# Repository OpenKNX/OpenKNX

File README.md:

# OpenKNX
OpenSource KNX software and hardware for maker, hobbyist and home automation enthusiasts

[Find all information in the Wiki](https://github.com/OpenKNX/OpenKNX/wiki)

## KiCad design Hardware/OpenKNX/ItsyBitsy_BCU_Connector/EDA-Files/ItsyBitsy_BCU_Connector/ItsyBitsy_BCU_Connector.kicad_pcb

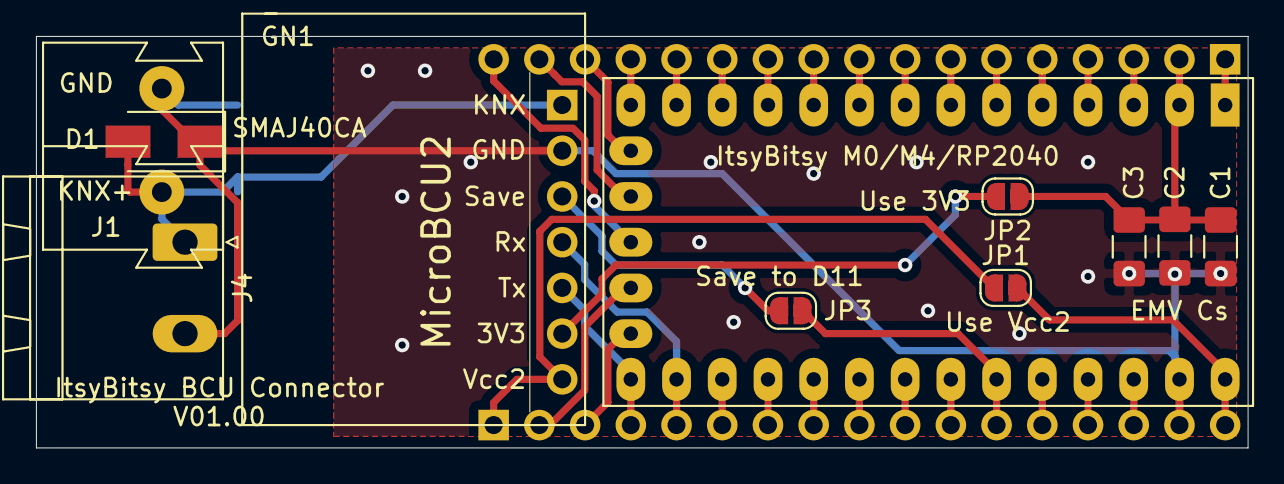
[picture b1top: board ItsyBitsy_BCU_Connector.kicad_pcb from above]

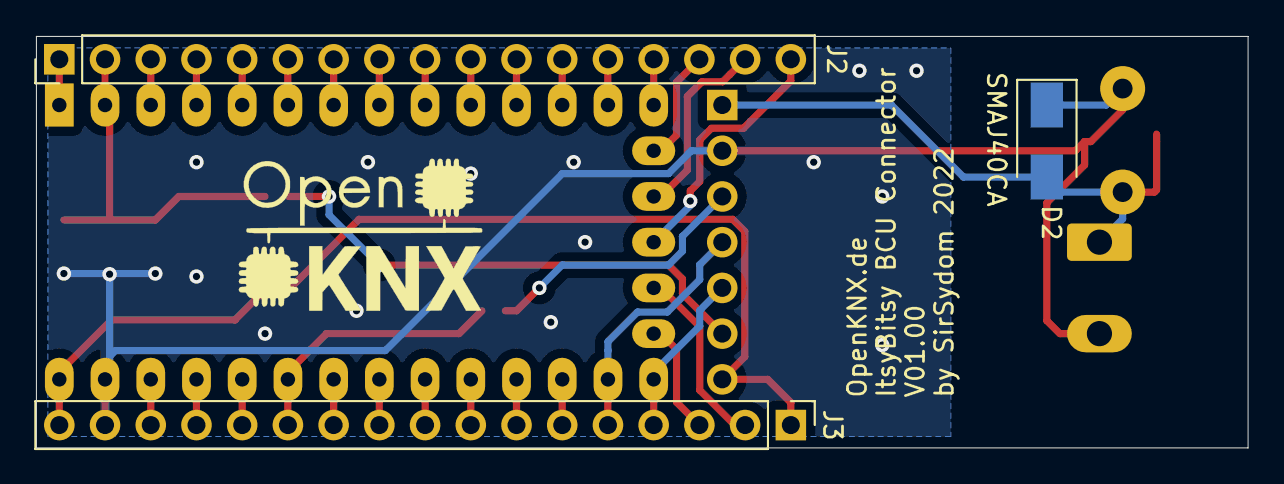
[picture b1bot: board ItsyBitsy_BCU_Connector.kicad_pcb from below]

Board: 2 copper layers, 67.3 x 22.9 mm, 14 parts (3 on the bottom side), 37 nets.

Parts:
C1, C2, C3: C; C_1206_3216Metric_Pad1.42x1.75mm_HandSolder
D1, D2: D_TVS; D_SMA
GN1: Konnekting_µBCU; MicroBCU2_PinSocket
GN2: ItsyBitsyM0
J1: Conn_KNX; KNX_Connector
J2, J3: Conn_01x17_Male; PinHeader_1x17_P2.54mm_Vertical
J4: Conn_KNX; PhoenixContact_MSTBA_2,5_2-G-5,08_1x02_P5.08mm_Horizontal
JP1, JP2, JP3: SolderJumper_2_Open; SolderJumper-2_P1.3mm_Open_RoundedPad1.0x1.5mm

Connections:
GND: C1.2, C2.2, C3.2, D1.1, D2.1, GN1.2, GN2.27, J1.2, J3.16, J4.2
unnamed: C1.1, C2.1, C3.1, GN2.2, J2.2, JP2.2
unnamed: D1.2, D2.2, GN1.1, J1.1, J4.1
unnamed: GN1.3, JP3.1
unnamed: GN1.6, JP2.1
unnamed: GN2.1, J2.1
unnamed: GN2.3, J2.3
unnamed: GN2.4, J2.4
unnamed: GN2.5, J2.5
unnamed: GN2.6, J2.6
unnamed: GN2.7, J2.7
unnamed: GN2.8, J2.8
unnamed: GN2.9, J2.9
unnamed: GN2.10, J2.10
unnamed: GN2.11, J2.11
unnamed: GN2.12, J2.12
unnamed: GN2.13, J2.13
unnamed: GN2.14, J2.14
unnamed: GN2.17, J3.6
unnamed: GN2.18, J3.7
unnamed: GN2.19, J3.8
unnamed: GN2.20, J3.9
unnamed: GN2.21, J3.10
unnamed: GN2.22, J3.11
unnamed: GN2.23, J3.12, JP3.2
unnamed: GN2.24, J3.13
unnamed: GN2.25, J3.14
unnamed: GN2.26, J3.15
unnamed: GN2.28, J3.17, JP1.2
unnamed: GN2.29, J2.15
unnamed: GN2.30, J2.16
unnamed: GN2.31, J2.17
unnamed: GN2.32, J3.2
unnamed: GN2.33, J3.3
Rx: GN1.5, GN2.15, J3.4
Tx: GN1.4, GN2.16, J3.5
Vcc2: GN1.7, J3.1, JP1.1

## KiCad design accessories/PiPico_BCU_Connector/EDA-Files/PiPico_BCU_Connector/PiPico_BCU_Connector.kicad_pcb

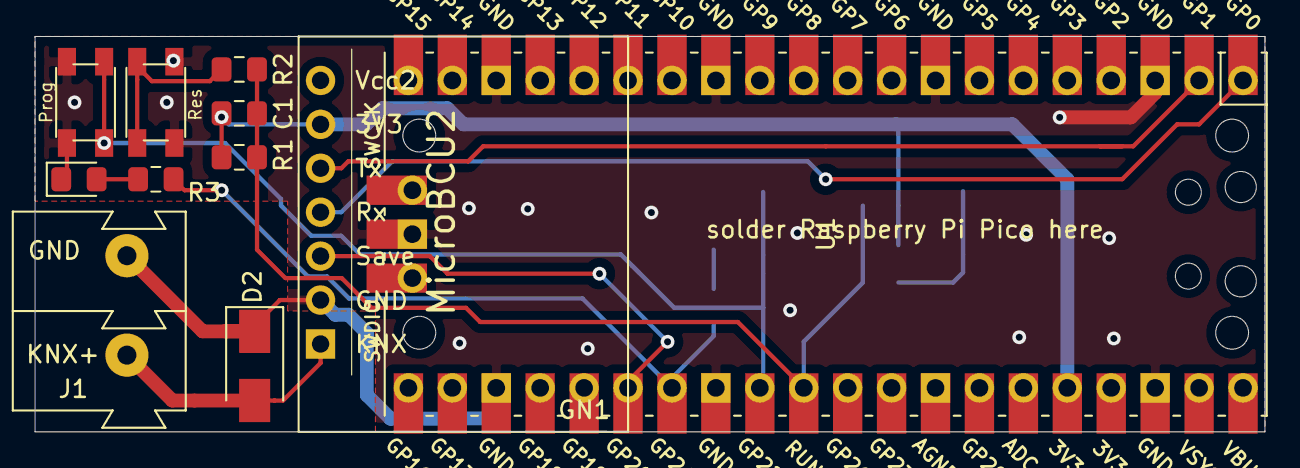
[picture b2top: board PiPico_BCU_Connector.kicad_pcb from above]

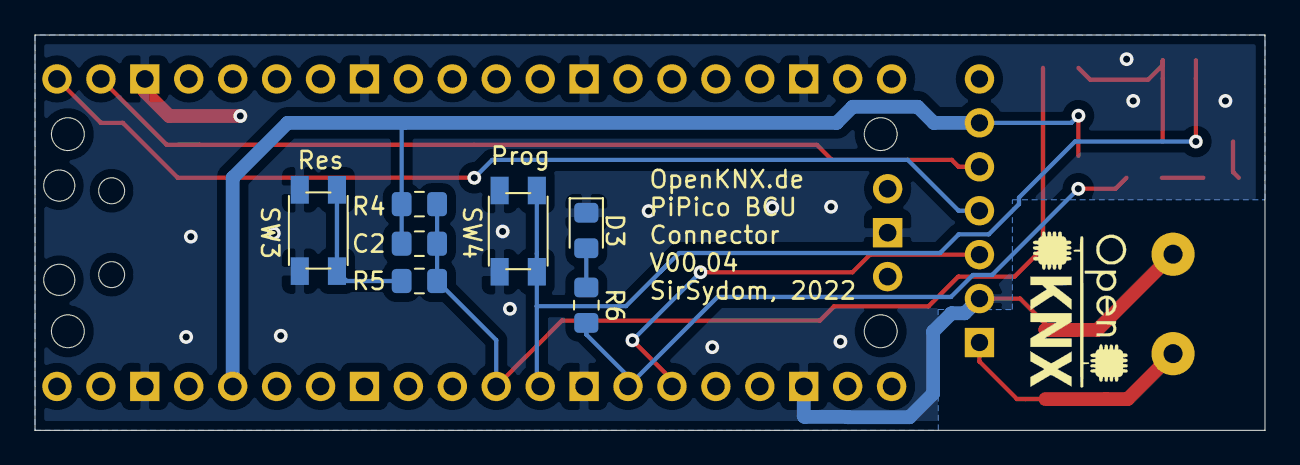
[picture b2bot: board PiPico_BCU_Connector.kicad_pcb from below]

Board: 2 copper layers, 71.1 x 22.9 mm, 18 parts (7 on the bottom side), 13 nets.

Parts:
C1, C2: 330pF; C_0805_2012Metric_Pad1.15x1.40mm_HandSolder
D1, D3: LED; D_0805_2012Metric_Pad1.15x1.40mm_HandSolder
D2: D_TVS; D_SMA
GN1: Konnekting_µBCU; MicroBCU2_PinSocket_LowProfile
J1: Conn_KNX; KNX_Connector
R1, R4: 2k2; R_0805_2012Metric_Pad1.15x1.40mm_HandSolder
R2, R5: 220; R_0805_2012Metric_Pad1.15x1.40mm_HandSolder
R3, R6: 1k; R_0805_2012Metric_Pad1.15x1.40mm_HandSolder
SW1, SW4: Prog; SW_Push_Xunpu_TS-1089S_Handsolder
SW2, SW3: Res; SW_Push_Xunpu_TS-1089S_Handsolder
U1: Pico; RPi_Pico_SMD_TH

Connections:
+3V3: C1.1, C2.1, GN1.6, R1.1, R4.1, U1.36
GND: D1.1, D2.1, D3.1, GN1.2, J1.2, SW1.2, SW2.2, SW3.2, SW4.2, U1.3, U1.8, U1.13, U1.18, U1.23, U1.28, U1.38, U1.42
unnamed: D1.2, R3.1
unnamed: D2.2, GN1.1, J1.1
unnamed: D3.2, R6.1
unnamed: GN1.3, U1.26
unnamed: R2.1, SW2.1
unnamed: R3.2, R6.2, U1.27
unnamed: R5.1, SW3.1
PROG: SW1.1, SW4.1, U1.29
RUN: C1.2, C2.2, R1.2, R2.2, R4.2, R5.2, U1.30
Rx: GN1.5, U1.2
Tx: GN1.4, U1.1

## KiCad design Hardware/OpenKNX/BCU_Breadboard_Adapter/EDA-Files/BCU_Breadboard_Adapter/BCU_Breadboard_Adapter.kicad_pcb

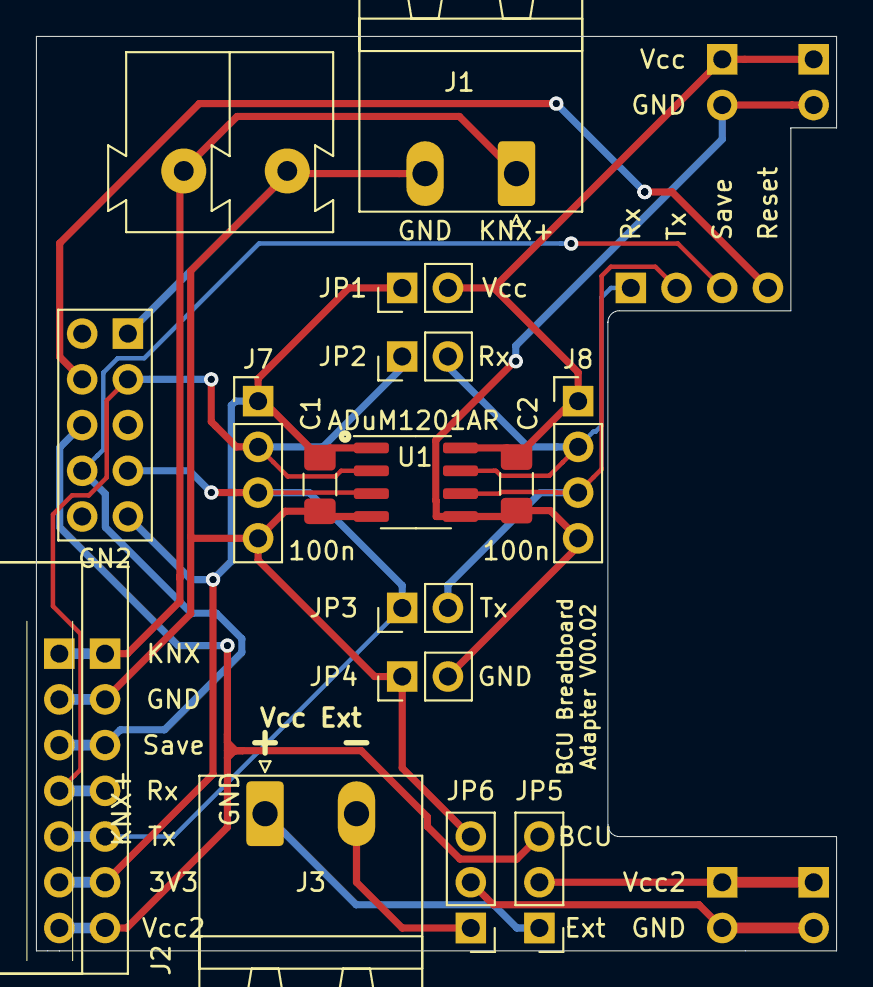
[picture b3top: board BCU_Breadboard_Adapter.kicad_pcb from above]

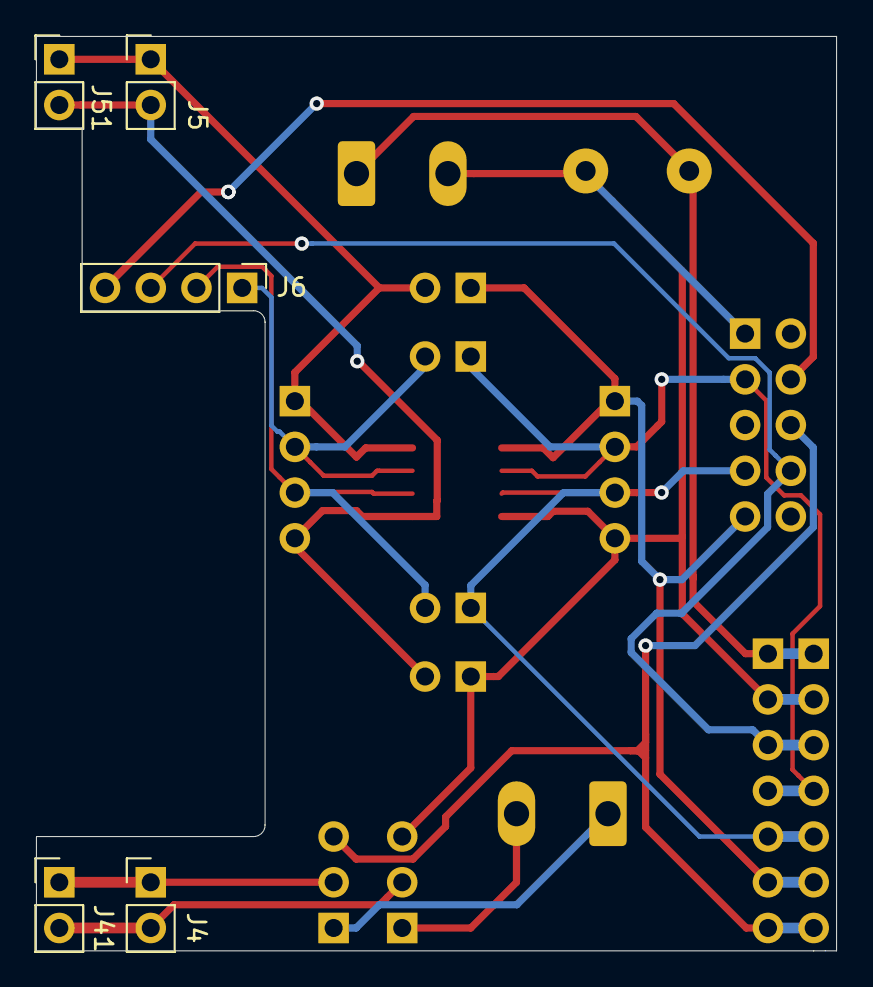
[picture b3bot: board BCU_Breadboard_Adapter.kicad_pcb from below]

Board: 2 copper layers, 44.5 x 50.8 mm, 22 parts (5 on the bottom side), 16 nets.

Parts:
C1, C2: 100n; C_1206_3216Metric_Pad1.42x1.75mm_HandSolder
GN1, GN3: Konnekting_µBCU; Konnekting_BCU
GN2: Siemens_BCU; Siemens_UP117_12_flat_header_only
J1: KNX_CC; PhoenixContact_MSTBA_2,5_2-G-5,08_1x02_P5.08mm_Horizontal
J2: KNX_Wago; KNX_Connector
J3: VCC_Ext; PhoenixContact_MSTBA_2,5_2-G-5,08_1x02_P5.08mm_Horizontal
J4, J41: VCC_Bot; PinHeader_1x02_P2.54mm_Vertical
J5, J51: VCC_Top; PinHeader_1x02_P2.54mm_Vertical
J6: BCU_Logik; PinHeader_1x04_P2.54mm_Vertical
J7, J8: Conn_01x04; PinHeader_1x04_P2.54mm_Vertical
JP1, JP2, JP3, JP4: Jumper; PinHeader_1x02_P2.54mm_Vertical
JP5, JP6: Jumper_NC_Dual; PinHeader_1x03_P2.54mm_Vertical
U1: ADuM1201AR; SOIC-8_3.9x4.9mm_P1.27mm

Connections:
unnamed: C1.1, GN1.6, GN2.5, GN3.6, J7.1, JP1.1, U1.1
unnamed: C1.2, GN1.2, GN2.1, GN3.2, J1.2, J2.2, J7.4, JP4.1, JP6.3, U1.4
unnamed: C2.1, J5.1, J8.1, J51.1, JP1.2, U1.8
unnamed: C2.2, J5.2, J8.4, J51.2, JP4.2, U1.5
unnamed: GN1.1, GN3.1, J1.1, J2.1
unnamed: GN1.3, GN2.7, GN3.3, J6.3
unnamed: GN1.4, GN2.2, GN3.4, J7.2, JP2.1, U1.2
unnamed: GN1.5, GN2.4, GN3.5, J7.3, JP3.1, U1.3
unnamed: GN1.7, GN2.8, GN3.7, JP5.3
unnamed: GN2.9, J6.4
unnamed: J3.1, JP5.1
unnamed: J3.2, JP6.1
unnamed: J4.1, J41.1, JP5.2
unnamed: J4.2, J41.2, JP6.2
unnamed: J6.1, J8.2, JP2.2, U1.7
unnamed: J6.2, J8.3, JP3.2, U1.6

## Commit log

2022-02-02 added profile readme
2022-02-02 Revert last try
2022-02-10 Update README.md
    finished device naming scheme
2022-02-15 added doc of adapter PCBs
2022-02-15 added NanoBCU and MicroBCU2 doc
2022-02-15 added PiPico BCU Connector pictures
2022-02-15 added thumbnail
2022-02-16 added pic
2022-02-17 ItsyBitsy_BCU_Connector_V01.00
2022-02-17 added docu
2022-02-18 added measurement for SAVE pin
2022-10-14 added Pico case 001
2022-10-14 added pics
2022-10-15 added schematic
2022-10-15 improved PiPico Case
2022-10-15 changed knx connector geometry
2022-10-15 moved to CATIA subdir
2023-11-08 NanoBCU V02.00 documentation
2024-07-27 KiCAD project files of - PiPico BCU Adapter - ItsyBitsy BCU Adapter - BCU Breadboard Adapter
2025-01-01 - Restructured directories same as in "OGM-HardwareConfig". - Added AB-SmartHouse Switch Actuator schematics. - Prepared directory for Smart-MF.
2025-01-01 Renamed now using device ID as folder name.
2025-03-27 add Smartmf Schematics
2025-03-29 Added schematics of AB-SmartHouse devices.
2025-04-26 Added schematics for AB-SmartHouse constant voltage dimmers.
2025-04-26 Added schematics for AB-SmartHouse push buttons.
2025-07-11 Added AB-TCH-RND schematics.
2025-12-14 Updated LED dimmer schematics.
2026-02-10 add SOM-Variants
2026-02-14 Updated AB-SmartHouse schematics.
